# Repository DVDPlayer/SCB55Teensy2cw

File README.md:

Disclaimer: I'm not a professional programmer or hardware engineer, so go easy on me, use at own risk!

Note: I know that the Teensy 2.0 is quite old, but I used it because I had it and for the challenge!
	Feel free to port it to another device. (Teensy 2.0 also has built-in support for USB-MIDI)

# 🚀 Teensy 2.0 Custom MIDI SBC-55 Controller Firmware (With Hardware Rev.1)

A playback prioritizing serial and USB MIDI firmware for the Teensy 2.0 platform featuring an OLED user interface, rotary encoder control (variable acceleration), Capital Tone Fallback (inverts bank# on fallback), drum and instrument tracking / setting per channel (354 instruments & 10 drum sets - all banks except 126), channel level settings (volume, reverb, chrous), global level settings (volume reverb, chrous), MT-32 emulation initialization (patch, pan, reverb, & pitch bend), display of MT-32 / SC-55 SysEx text messages, display of SC-55 SysEx graphics, send / receive GM & GS SysEx reset, 'analog' volume setting, all notes off Panic! feature, external (software driven) reset button, power-on reset of SCB-55, inactivity screen saver, and a dedicated MIDI hardware pipeline to the SCB-55 waveblaster module.  

Runs from USB (<350mA) or dedicated 6Vdc to 35Vdc input. (see Teensy MOD picture)

This repository contains only the core project firmware and hardware. All third-party dependencies are managed locally to keep the repository structure clean and as lightweight as possible.  

---

## 📦 Required Dependencies

Before compiling, make sure you have the following libraries installed via the Arduino Library Manager:
* **Adafruit_GFX** (OLED Core Graphics)
* **Adafruit_SSD1306** (OLED Driver)
* **Encoder** by Paul Stoffregen (Hardware Rotary Encoder tracking)

*Note: Core libraries (`Arduino.h`, `Wire.h`, `avr/pgmspace.h`, `util/delay.h`) are built into the Teensy / AVR toolchain and do not need to be installed manually.*

---

## 🛠️ Installation & Memory Optimization

To successfully fit the compiled firmware within the microcontroller's limited flash memory, you must disable the default Adafruit splash screen to save code space.

This project is shared under the **GNU GPLv3** license, and since third-party libraries are not hosted directly in this repository, you will need to apply the following optimizations to your local Arduino environment manually:

### Required Tweaks:
1. Locate your local Arduino libraries folder (usually found under `Documents/Arduino/libraries/`).
2. Open the `Adafruit_SSD1306` directory.
3. Open `Adafruit_SSD1306.h` in a text editor.
4. Locate the configuration lines near the top of the file and **uncomment** the splash logo macro definition to match this:
```   
   // Uncomment to disable Adafruit splash logo
   #define SSD1306_NO_SPLASH
```   
5. Open the Arduino `usb_api.h` in a text editor and change `#define USB_MIDI_SYSEX_MAX 64` to at least 79

(Location example: `c:\users\<username>\AppData\Local\Arduino15\packages\teensy\hardware\avr\1.61.0\cores\usb_midi`)

6. Go back one directory to the `cores` folder and open the `teensy` folder and Edit `HardwareSerial.cpp`

7. Find and change the following two lines: (Note: `RX_BUFFER_SIZE` was `64` which is too small for long SysEx)
```
#define RX_BUFFER_SIZE 128 
#define SERIAL1_TX_BUFFER_SIZE 256
```
8. After saving the above files you can compile the project in your Arduino IDE (`Board:Teensy2.0` `USB Type:MIDI`).

---

## 🔌 Hardware Pinout (Basic Info - or if not using my board design)

Connect your components to the **Teensy 2.0** board according to the pinout layout below:

| Component 		| Pin 		| Teensy 2.0 Pin| Notes |
| :--- | :---: | :---: | ---: |
| **SSD1306 OLED**	| GND 		| GND		| (Check pinout as some OLEDs are backwards!)|
|			| VCC 5V	| VCC 5V	|	|
| 			| SCL 		| **5**  (PD0)	| I2C Clock (`Wire.h`)|
| 			| SDA 		| **6**  (PD1)	| I2C Data  (`Wire.h`)|
|			|		|		|	|
| **Rotary Encoder**	| Pin A  	| **1**  (PB1)	| Main rotation pin|
| encoder module used	| Pin B  	| *24**  (PE6)	| Main rotation pin|
|			| Switch 	| **0**  (PB0)	| Encoder push-button switch|
|			| VCC		| VCC		|	|
|			| GND		| GND		|	|
|			|		|		|	|
| **Vol POT 10k-100k**	| Wiper Pin 	| **12** (PD7)	| 'Analog' Output Control (Volume potentiometer)|
|   Right Pin		| VCC		| VCC		| (optional part)|
|   Left  Pin		| GND		| GND		|	|
|			|		|		|	|
| **Reset Button** 	| Switch Pin 	| **10** (PC7)	| System Reset trigger|
|			| GND		| GND		| (optional part)|
|			|		|		|	|
| **Reset to SCB55**	| Reset Line 	| **2**  (PB2)	| Hardware reset line sent to SCB-55 - pin 26|
|			|		|		|	|
| **Serial MIDI RX** 	| MIDI IN Line	| **RX (Pin 7)**| (PD2) Hardware MIDI input (from H11L1+470Ω pull-up)|
|			|		|		|	|
| **SCB-55 MIDI RX** 	| MIDI OUT Line	| **TX (Pin 8)**| (PD3) MIDI stream to Roland SCB-55 - pin 4|

 Note: 	Pin numbers are programming numbers, add 2 for actual pin number except 24 = pin30, 12 = pin19.
	If you want to use external power and USB, the Teensy 2.0 must be modified. (see Teensy MOD picture)
	The SCB-55 also requires a +/-12V and +5 supply to run correctly along with L/R audio out.

		MIDI Input Example:

(Note: The Ultra-cheap USB MIDI cables, with the treble clef, will corrupt all SysEx messages.)

---

## 🎹 MIDI & Serial Routing Architecture
* **Serial RX (Receive) :** Dedicated to handling incoming **MIDI In** streams.
* **USB MIDI  (Bi-directional):** to/from Teensy 2.0 (MIDI actions are echoed from UI to host PC)
* **Serial TX (Transmit):** Dedicated to delivering processed **MIDI data to the SCB-55** waveblaster module.

---

## 💻 MENUS, Teensy 2.0 Vusb mod, Rev1 Diode Mod (important) and other pictures

	Arduino IDE Settings
  
	 <b>Hardware</b> 

	 <b>User Interface</b> 

| | |
| :---: | :---: |
|  |  |
	 Important if using dual power (*Teensy MOD) 
   
	 <b>Initial Prototype</b> 

 <b>If using rev1 hardware (update coming)</b> 

---

## 📄 Credits and other notes

This used: 

Arduino IDE 2.3.10 - [IDE](https://www.arduino.cc/en/software/),  [Teensy2.0](https://www.pjrc.com/teensy/card2a_rev5_web.pdf)

KiCAD 10.0 (Along with several Footprints, please let me know if I missed credit on any), [KiCad](https://github.com/KiCad)

Teensy 2.0 Footprint [XenGi](https://github.com/XenGi/teensy_library)

FreeCAD 1.1.1 (to be used for the 3D case) - [FreeCAD](https://www.freecad.org/)

along with several programs that were very helpful for debug and testing:

The excellent MIDI Player 6.5 by Zoltán Bacskó (Falcosoft) https://falcosoft.hu/

The very impressive Nuked-SC55 emulator which helped verify proper display & behaviour. [Nuked-SC55](https://github.com/nukeykt/Nuked-SC55) 

Along with Roland who created the SCB-55 GS Daughter Board that made this possible.

Other GS/GM daughter boards that use the wavetable connection should be electrically compatible, but the firmware is written for the SCB-55 and would need to be modified to control others properly.  Also the board and corner holes have been sized for the SCB-55 specifically.  Feel free to make your own modifications.

---

## 📜 License

This project is licensed under the **GNU General Public License v3 (GPLv3)**. See the `LICENSE` file in the root of this repository for the full legal text. You are free to share and adapt this code, provided all derivative works remain open-source under the same terms.

## ⚙️ **Third-Party Libraries:** This software compiles dependencies from the **Arduino Core Library Framework** (LGPL-2.1) and the **Adafruit GFX Engine** (BSD 2-Clause). Full attribution terms are listed inside the [`THIRD-PARTY-NOTICES.md`](./THIRD-PARTY-NOTICES.md) file.

---

Please Note:

This is Rev.1, there are some hardware errors (POT wired backwards & I should have used a WRA0512S (not A0512S))
also I'm just about out of code space in the Teensy 2.0, but it does seem to be working quite well (with the mod of adding an inline 1N5819 in front of the A0512S on the 5V line to drop +/-12V to a safe level).  This diode bodge sacrifices the dual colour LED that I was planning, but it wasn't correct anyhow. 
(Don't get AI to 'help' design hardware without verifying results!)

This does work fully from USB only (< 350mA), or from external power with 5 pin MIDI, when connected to USB the MIDI jack is still active and either can be used (one at a time as there is no flow control).  Connecting USB and external power should be safe* as I've used an ORing module to prevent voltage feedback/feedthrough, but currently you will lose USB connection with the host PC (not sure if this can be fixed, but a powered hub can be used for a weak USB port in place of the external power jack).  *As long as the Teensy's `Vusb` is cut and wired to the board!

I plan on addressing the current hardware errors on the board and will see if I can optimize the code further as I do have some inconsistencies and some duplication in the code.  I also have a few more features to add (making the POT re-assignable, and various settings saved to EEPROM, etc.) I would also like to implement the display of bank 126 (but doubt there will be enough code space for this).

Any modifications or suggestions are welcome, please remember that I don't do this professionally and I did enlist AI input / modification for some of my code, so it may not be the best implementation possible. 

Once again, this works for me, but I take no liability or responsibility if any thing blows up or burns down and you assume all responsibility for creating all or parts of this project.

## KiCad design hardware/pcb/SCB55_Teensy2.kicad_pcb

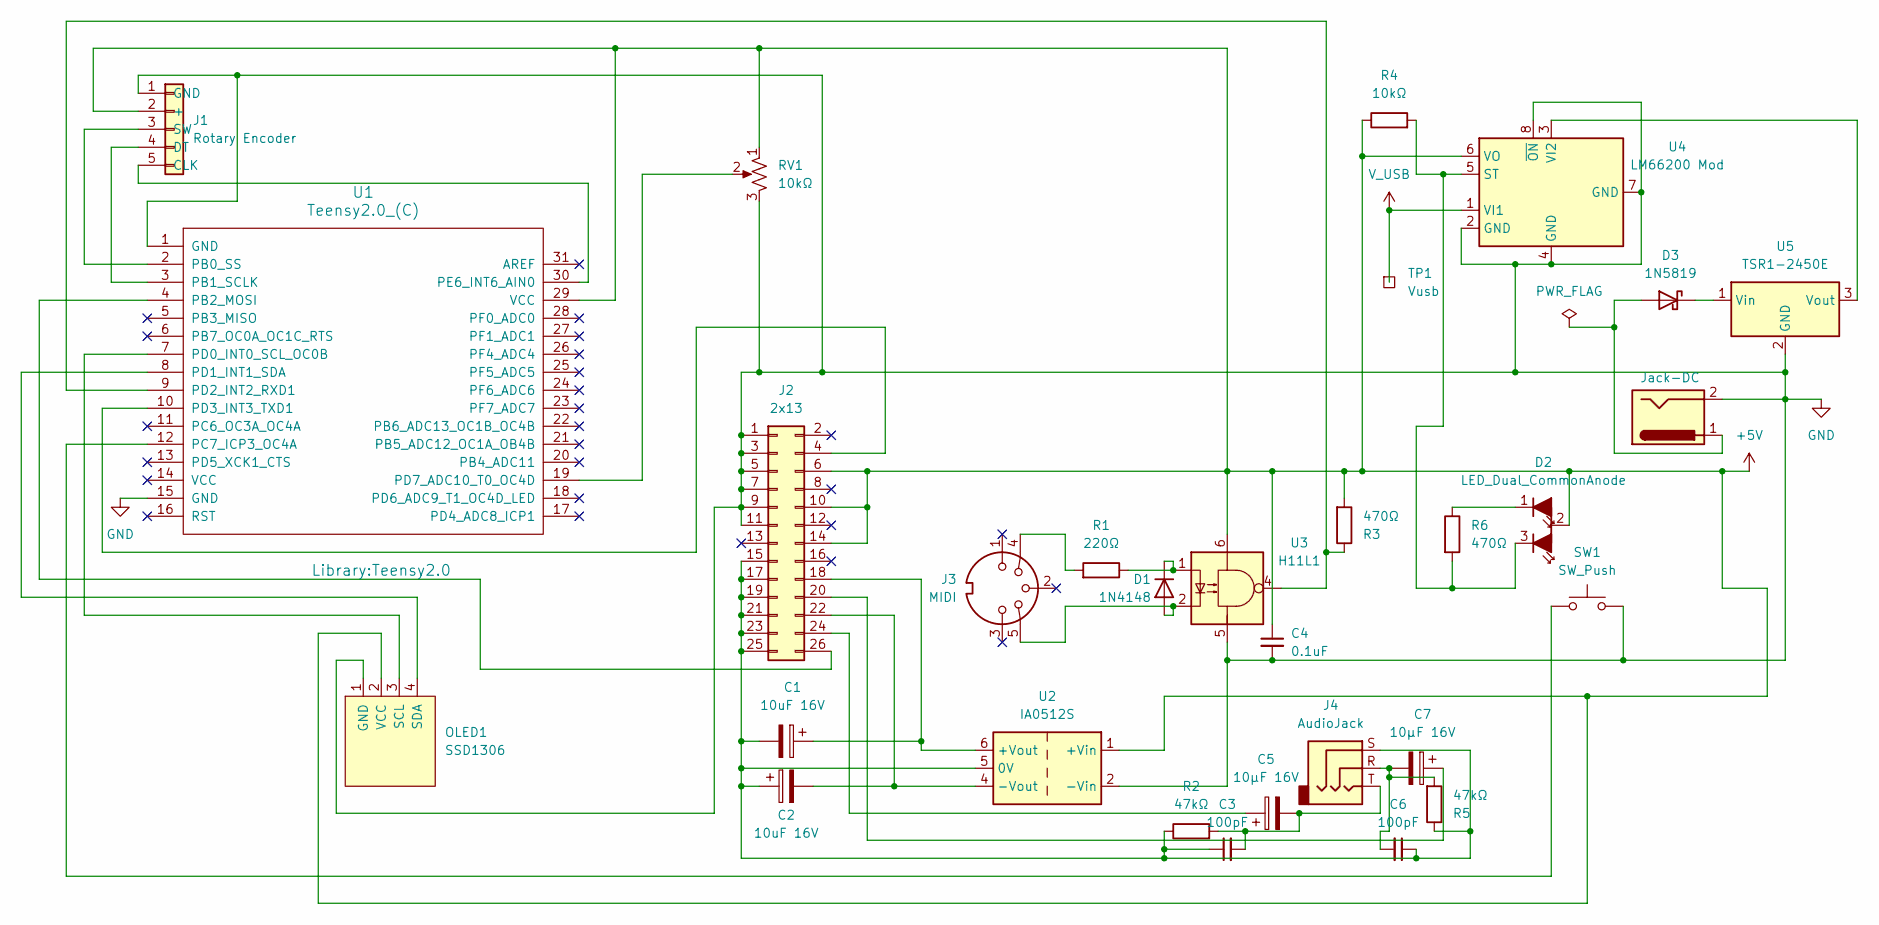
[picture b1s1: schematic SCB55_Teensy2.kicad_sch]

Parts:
C1, C2: 10uF 16V; CP_Radial_D5.0mm_P2.00mm
C3, C6: 100pF; CP_Radial_D4.0mm_P1.50mm
C4: 0.1uF; CP_Radial_D4.0mm_P1.50mm
C5, C7: 10µF 16V; CP_Radial_D5.0mm_P2.00mm
D1: 1N4148; D_DO-35_SOD27_P7.62mm_Horizontal
D2: LED_Dual_CommonAnode; LED_3Pin_2.54mm
D3: 1N5819; D_DO-41_SOD81_P10.16mm_Horizontal
J1: Rotary Encoder; Rotary Encoder Board with Switch
J2: 2x13; PinHeader_2x13_P2.54mm_Vertical
J3: MIDI; DIN5_MIDI
J4: AudioJack; Jack_3.5mm_Ledino_KB3SPRS_Horizontal
J5: Jack-DC; BarrelJack_Horizontal
OLED1: SSD1306; 128x64OLED
R1: 220Ω; R_Axial_DIN0207_L6.3mm_D2.5mm_P2.54mm_Vertical
R2, R5: 47kΩ; R_Axial_DIN0207_L6.3mm_D2.5mm_P2.54mm_Vertical
R3, R6: 470Ω; R_Axial_DIN0207_L6.3mm_D2.5mm_P2.54mm_Vertical
R4: 10kΩ; R_Axial_DIN0207_L6.3mm_D2.5mm_P2.54mm_Vertical
RV1: 10kΩ; WH148 Potentiometer 3 Pin
SW1: SW_Push; SW_PUSH_6mm
TP1: Vusb; TestPoint_THTPad_2.0x2.0mm_Drill1.0mm
U1: Teensy2.0_(C); Teensy2.0
U2: IA0512S; Converter_DCDC_XP_POWER-IAxxxxS_THT
U3: H11L1; DIP-6_W7.62mm
U4: LM66200 Mod; DIP-8_W7.62mm
U5: TSR1-2450E; Converter_DCDC_TRACO_TSR1-xxxxE_THT

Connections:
+5V: C4.1, D2.2 (A), J1.2 (+), J2.6, J2.10, J2.14, OLED1.2 (VCC), R3.2, R4.1, RV1.1, U1.29 (VCC), U2.1 (+Vin), U3.6, U4.6 (VO)
GND: C4.2, J1.1 (GND), J2.1, J2.3, J2.5, J2.7, J2.9, J2.11, J5.2, OLED1.1 (GND), RV1.3, SW1.2, U1.1 (GND), U1.15 (GND), U2.2 (-Vin), U3.5, U4.2 (GND), U4.4 (GND), U4.7 (GND), U4.8 (~ON), U5.2 (GND)
unnamed: C3.2, C5.2, J4.T, R2.2
unnamed: C6.2, C7.2, J4.R, R5.2
unnamed: D1.2 (A), J3.5, U3.2
unnamed: D1.1 (K), R1.1, U3.1
unnamed: D2.1 (K1), R6.1
unnamed: D2.3 (K2), R4.2, R6.2, U4.5 (ST)
unnamed: D3.2 (A), J5.1
unnamed: D3.1 (K), U5.1 (Vin)
unnamed: J1.5 (CLK), U1.30 (PE6_INT6_AIN0)
unnamed: J1.4 (DT), U1.3 (PB1_SCLK)
unnamed: J1.3 (SW), U1.2 (PB0_SS)
unnamed: J2.4, U1.10 (PD3_INT3_TXD1)
unnamed: C1.2, C2.1, C3.1, C6.1, J2.15, J2.17, J2.19, J2.21, J2.23, J2.25, J4.S, R2.1, R5.1, U2.5 (0V)
unnamed: C1.1, J2.18, U2.6 (+Vout)
unnamed: C7.1, J2.20
unnamed: C2.2, J2.22, U2.4 (-Vout)
unnamed: C5.1, J2.24
unnamed: J2.26, U1.4 (PB2_MOSI)
unnamed: J3.4, R1.2
unnamed: OLED1.3 (SCL), U1.7 (PD0_INT0_SCL_OC0B)
unnamed: OLED1.4 (SDA), U1.8 (PD1_INT1_SDA)
unnamed: SW1.1, U1.12 (PC7_ICP3_OC4A)
unnamed: R3.1, U1.9 (PD2_INT2_RXD1), U3.4
unnamed: RV1.2, U1.19 (PD7_ADC10_T0_OC4D)
unnamed: U4.3 (VI2), U5.3 (Vout)
V_USB: TP1.1 (1_1), U4.1 (VI1)

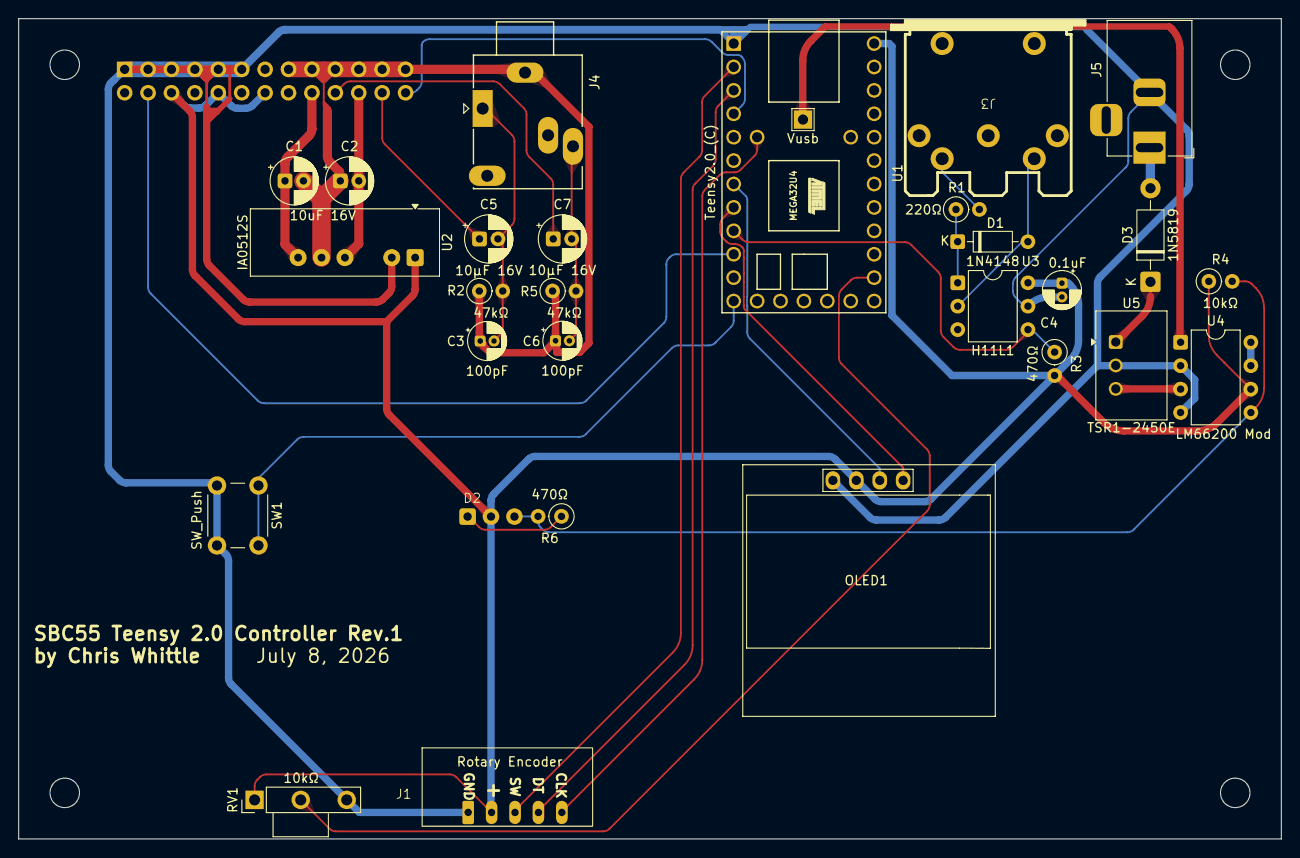
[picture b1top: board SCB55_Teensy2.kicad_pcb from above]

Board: 2 copper layers, 137.0 x 89.0 mm, 30 parts (1 on the bottom side), 28 nets.
